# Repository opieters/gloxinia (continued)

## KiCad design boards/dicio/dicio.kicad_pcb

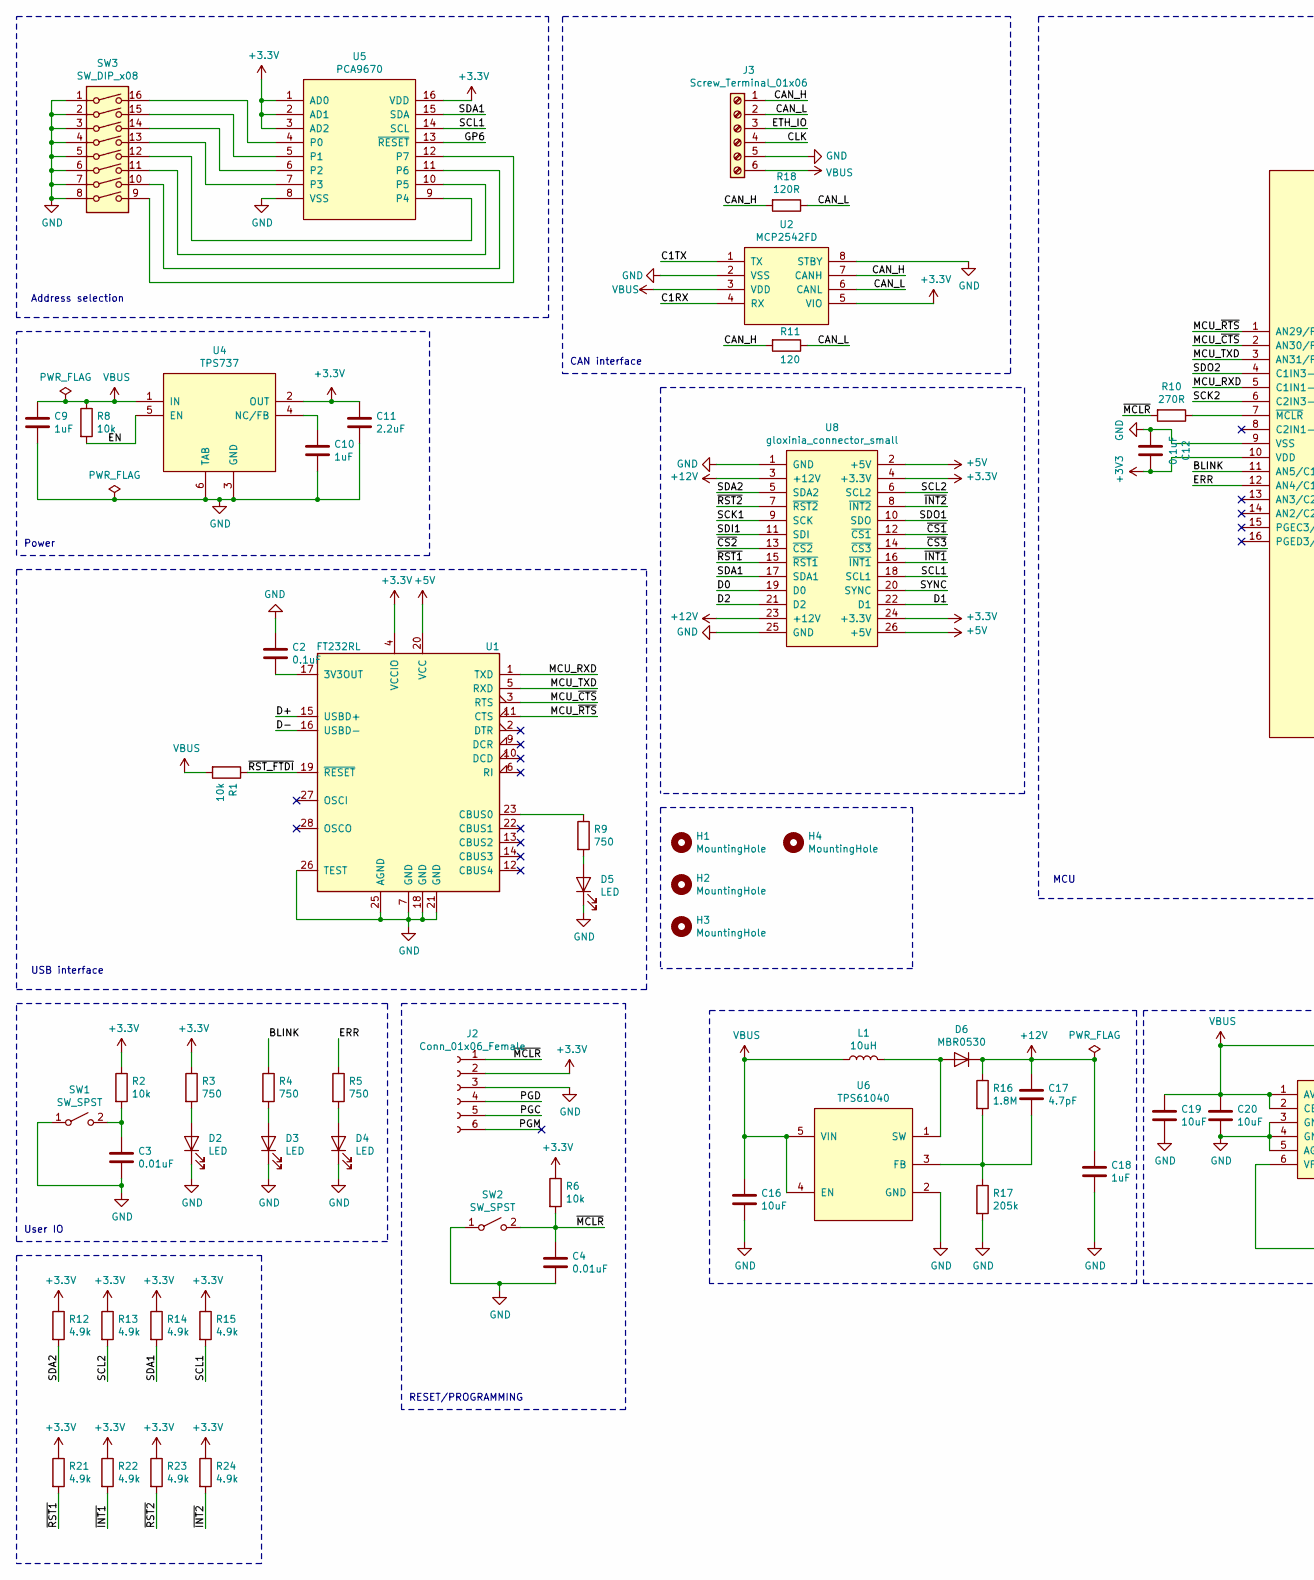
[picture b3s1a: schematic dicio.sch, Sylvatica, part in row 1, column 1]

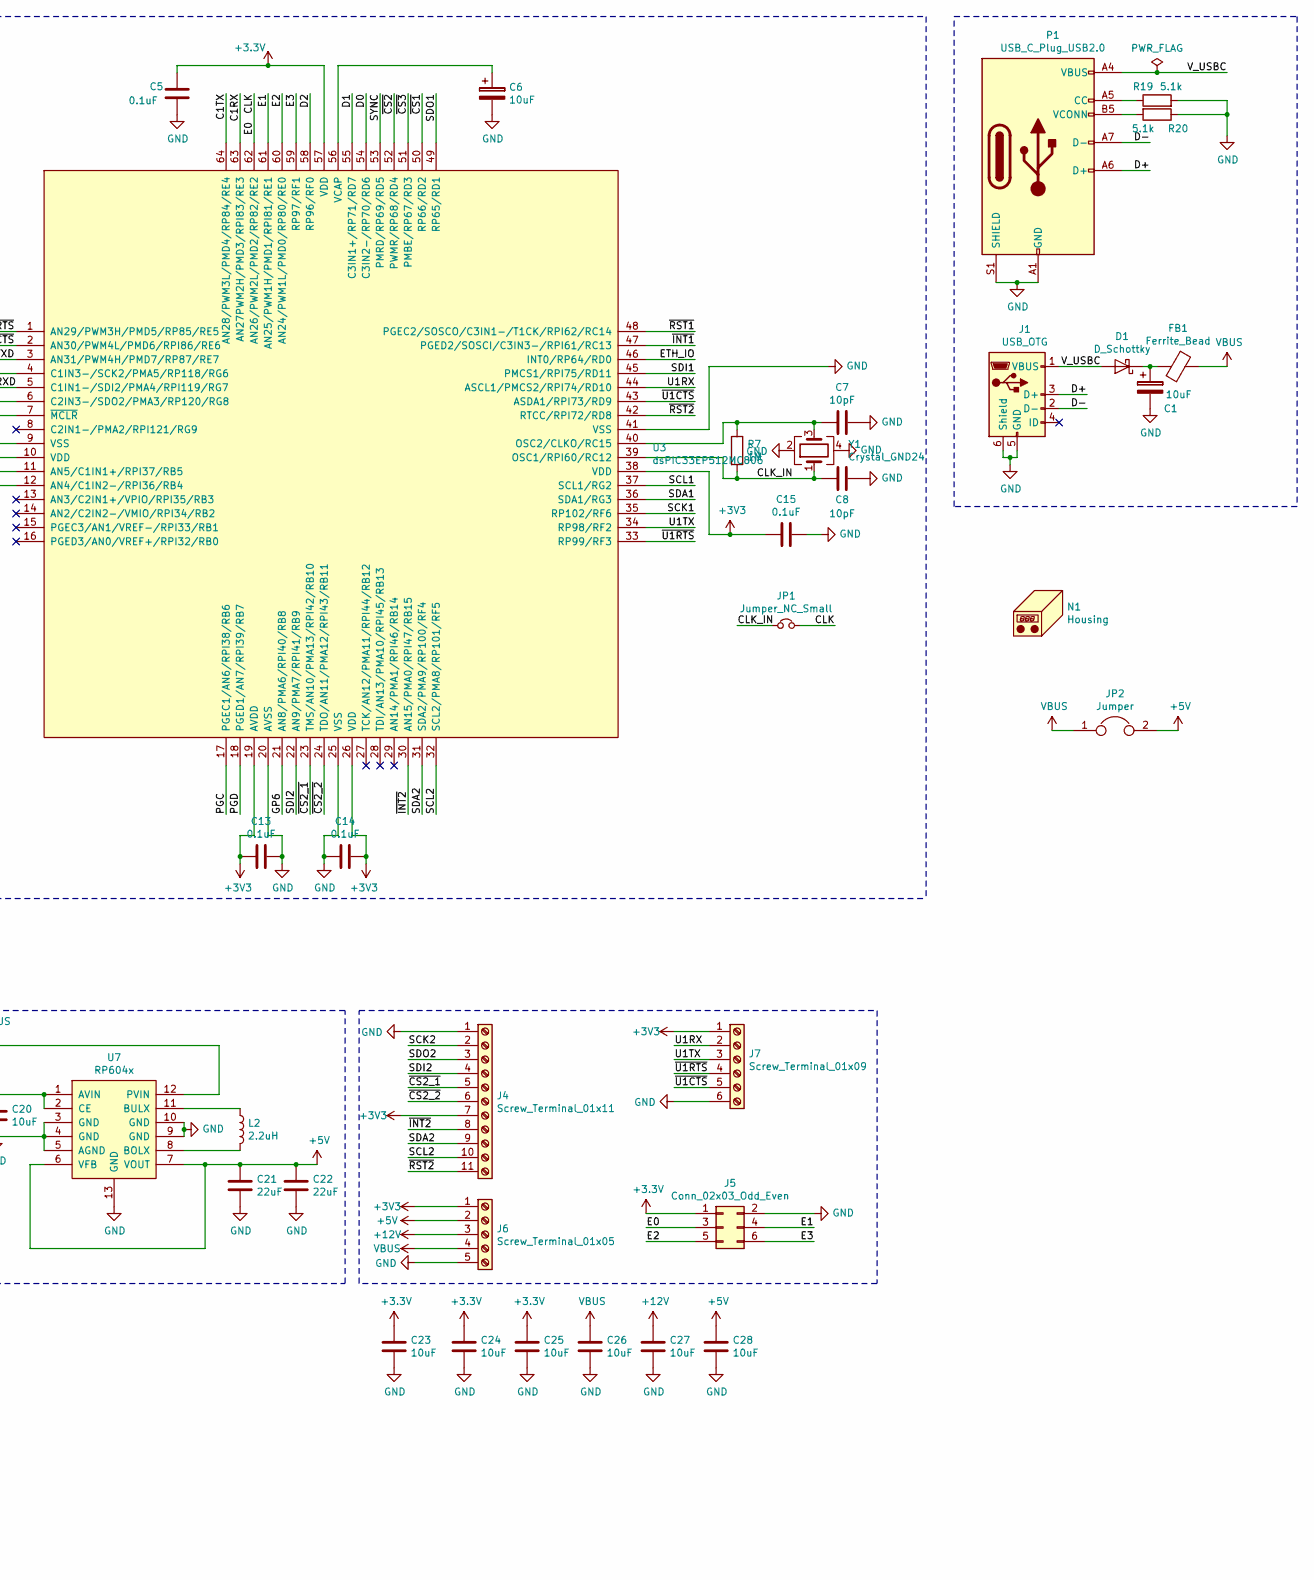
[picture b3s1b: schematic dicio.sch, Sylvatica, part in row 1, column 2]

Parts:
C1, C6, C16, C19, C20, C23, C24, C25, C26, C27, C28: 10uF; C_1210_3225Metric; Mouser 963-TMK325BJ106KM-P
C2, C5, C12, C13, C14, C15: 0.1uF; C_0603_1608Metric; Mouser 710-885012206071
C3, C4: 0.01uF; C_0603_1608Metric; Mouser 710-885012206065
C7, C8: 10pF; C_0603_1608Metric; Mouser 603-CC603FRNPO9BN100
C9, C10, C18: 1uF; C_0603_1608Metric; Mouser 963-TMK325B7105KD-T
C11: 2.2uF; C_1206_3216Metric; Mouser 791-1206X225K250CT
C17: 4.7pF; C_0603_1608Metric; Mouser 710-885012006049
C21, C22: 22uF; C_1210_3225Metric; Mouser 963-TMK316BBJ226ML-T
D1: D_Schottky; D_SMB; Mouser 621-B340LB-F
D2, D3, D4, D5: LED; LED_0603_1608Metric; Mouser 78-TLMS1000
D6: MBR0530; D_SOD-123; Mouser 512-MBR0530
FB1: Ferrite_Bead; L_0805_2012Metric; Mouser 875-MI0805K400R-10
H1, H2, H3, H4: MountingHole; MountingHole_3.2mm_M3
J1: USB_OTG; USB_Micro-B_Molex-105017-0001; Mouser 538-105017-0001
J2: Conn_01x06_Female; PinSocket_1x06_P2.54mm_Vertical
J3: Screw_Terminal_01x06; TB003-500-06; Mouser 490-TB003-500-P06BE
J4: Screw_Terminal_01x11; TB003-500-11; Mouser 490-TB003-500-P11BE
J5: Conn_02x03_Odd_Even; PinHeader_2x03_P2.54mm_Vertical
J6: Screw_Terminal_01x05; TB003-500-05; Mouser 490-TB003-500-P05BE
J7: Screw_Terminal_01x09; TB003-500-06; Mouser 490-TB003-500-P06BE
JP1: Jumper_NC_Small; SolderJumper-2_P1.3mm_Open_RoundedPad1.0x1.5mm
JP2: Jumper; SolderJumper-2_P1.3mm_Open_RoundedPad1.0x1.5mm
L1: 10uH; L_6.5mmx4.5mm_Bourns; Mouser 652-SDR0703-100KL
L2: 2.2uH; L_L4mm_D4mm_H1.8mm; Mouser 875-TYS40182R2M-10
N1: Housing; Enclosure-Hammond-1554LA; Mouser 546-1554LA2GYCL
P1: USB_C_Plug_USB2.0; USB_C_Receptacle_Amphenol_12401832E402A; Mouser 523-12401832E402A
R1, R2, R6, R8: 10k; R_0603_1608Metric; Mouser 284-APC0603B10K0N
R3, R4, R5, R9: 750; R_0603_1608Metric; Mouser 603-RC0603FR-07750RL
R7: 1M; R_0603_1608Metric; Mouser 603-RC0603FR-101ML
R10: 270R; R_0603_1608Metric; Mouser 603-RC0603FR-07270RL
R11: 120; R_0603_1608Metric; Mouser 71-CRCW0603120RFKEAC
R12, R13, R14, R15, R21, R22, R23, R24: 4.9k; R_0603_1608Metric; Mouser 603-RC0603FR-0724K9L
R16: 1.8M; C_0603_1608Metric; Mouser 603-AC0603FR-071M8L
R17: 205k; C_0603_1608Metric; Mouser 603-RC0603FR-07205KL
R18: 120R; R_Axial_DIN0204_L3.6mm_D1.6mm_P7.62mm_Horizontal; Mouser 594-5063JD120R0F
R19, R20: 5.1k; R_0603_1608Metric; Mouser 603-AC0603FR-135K1L
SW1, SW2: SW_SPST; SW_SPST_KMR2; Mouser 611-KMR621NGLFS
SW3: SW_DIP_x08; SW_DIP_SPSTx08_Slide_Omron_A6H-8101_W6.15mm_P1.27mm; Mouser 653-A6H-8101
U1: FT232RL; SSOP-28_5.3x10.2mm_P0.65mm; Mouser 895-FT232RL
U2: MCP2542FD; SOIC-8_3.9x4.9mm_P1.27mm; Mouser 579-MCP2542FDT-E/SN
U3: dsPIC33EP512MC806; TQFP-64_10x10mm_P0.5mm; Mouser 579-33EP512MC806IPT
U4: TPS737; SOT-223-6; Mouser 595-TPS73733DCQR
U5: PCA9670; TSSOP-16_4.4x5mm_P0.65mm; Mouser 771-PCA9670PW118
U6: TPS61040; SOT-23-5; Mouser 595-TPS61040DBVR
U7: RP604x; DFN_12_Pin_2.7x3mm_P0.5mm; Mouser 848-RP604K501A-TR
U8: gloxinia_connector_small; PinHeader_2x13_P2.54mm_Vertical; Mouser 200-SSQ11303TD
Y1: Crystal_GND24; Crystal_SMD_Abracon_ABM3B-4Pin_5.0x3.2mm; Mouser 520-80-10-30B-CWNT

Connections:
+5V: C21.1, C22.1, C28.1, J6.2, JP2.2, U1.20 (VCC), U7.6 (VFB), U7.7 (VOUT), U8.2 (+5V), U8.26 (+5V)
+12V: C17.1, C18.1, C27.1, D6.1 (K), J6.3, R16.1, U8.3 (+12V), U8.23 (+12V)
/BLINK: R4.1, U3.11 (AN5/C1IN1+/RPI37/RB5)
/C1RX: U2.4 (RX), U3.63 (AN27PWM2H/PMD3/RPI83/RE3)
/C1TX: U2.1 (TX), U3.64 (AN28/PWM3L/PMD4/RP84/RE4)
/CAN_H: J3.1, R11.2, R18.2, U2.7 (CANH)
/CAN_L: J3.2, R11.1, R18.1, U2.6 (CANL)
/CLK: J3.4, J5.3, JP1.2, U3.62 (AN26/PWM2L/PMD2/RP82/RE2)
/CLK_IN: C8.2, JP1.1, R7.2, U3.39 (OSC1/RPI60/RC12), Y1.1
/D0: U3.54 (C3IN2-/RP70/RD6), U8.19 (D0)
/D1: U3.55 (C3IN1+/RP71/RD7), U8.22 (D1)
/D2: U3.58 (RP96/RF0), U8.21 (D2)
/D+: J1.3 (D+), P1.A6 (D+), U1.15 (USBD+)
/D-: J1.2 (D-), P1.A7 (D-), U1.16 (USBD-)
/E1: J5.4, U3.61 (AN25/PWM1H/PMD1/RPI81/RE1)
/E2: J5.5, U3.60 (AN24/PWM1L/PMD0/RP80/RE0)
/E3: J5.6, U3.59 (RP97/RF1)
/EN: R8.2, U4.5 (EN)
/ERR: R5.1, U3.12 (AN4/C1IN2-/RPI36/RB4)
/ETH_IO: J3.3, U3.46 (INT0/RP64/RD0)
/GP6: U3.21 (AN8/PMA6/RPI40/RB8), U5.13 (~RESET)
/MCU_RXD: U1.1 (TXD), U3.5 (C1IN1-/SDI2/PMA4/RPI119/RG7)
/MCU_TXD: U1.5 (RXD), U3.3 (AN31/PWM4H/PMD7/RP87/RE7)
/MCU_~CTS: U1.3 (RTS), U3.2 (AN30/PWM4L/PMD6/RPI86/RE6)
/MCU_~RTS: U1.11 (CTS), U3.1 (AN29/PWM3H/PMD5/RP85/RE5)
/PGC: J2.5, U3.17 (PGEC1/AN6/RPI38/RB6)
/PGD: J2.4, U3.18 (PGED1/AN7/RPI39/RB7)
/PGM: J2.6
/SCK1: U3.35 (RP102/RF6), U8.9 (SCK)
/SCK2: J4.2, U3.6 (C2IN3-/SDO2/PMA3/RP120/RG8)
/SCL1: R15.2, U3.37 (SCL1/RG2), U5.14 (SCL), U8.18 (SCL1)
/SCL2: J4.10, R13.2, U3.32 (SCL2/PMA8/RP101/RF5), U8.6 (SCL2)
/SDA1: R14.2, U3.36 (SDA1/RG3), U5.15 (SDA), U8.17 (SDA1)
/SDA2: J4.9, R12.2, U3.31 (SDA2/PMA9/RP100/RF4), U8.5 (SDA2)
/SDI1: U3.45 (PMCS1/RPI75/RD11), U8.11 (SDI)
/SDI2: J4.4, U3.22 (AN9/PMA7/RPI41/RB9)
/SDO1: U3.49 (RP65/RD1), U8.10 (SDO)
/SDO2: J4.3, U3.4 (C1IN3-/SCK2/PMA5/RP118/RG6)
/SYNC: U3.53 (PMRD/RP69/RD5), U8.20 (SYNC)
/U1RX: J7.2, U3.44 (ASCL1/PMCS2/RPI74/RD10)
/U1TX: J7.3, U3.34 (RP98/RF2)
/V_USBC: D1.2 (A), J1.1 (VBUS), P1.A4 (VBUS), P1.A9 (VBUS), P1.B4 (VBUS), P1.B9 (VBUS)
/~CS1: U3.50 (RP66/RD2), U8.12 (~CS1)
/~CS2: U3.52 (PWMR/RP68/RD4), U8.13 (~CS2)
/~CS2_1: J4.5, U3.23 (TMS/AN10/PMA13/RPI42/RB10)
/~CS2_2: J4.6, U3.24 (TDO/AN11/PMA12/RPI43/RB11)
/~CS3: U3.51 (PMBE/RP67/RD3), U8.14 (~CS3)
/~INT1: R22.2, U3.47 (PGED2/SOSCI/C3IN3-/RPI61/RC13), U8.16 (~INT1)
/~INT2: J4.8, R24.2, U3.30 (AN15/PMA0/RPI47/RB15), U8.8 (~INT2)
/~MCLR: C4.1, J2.1, R6.2, R10.2, SW2.2 (B)
/~RST1: R21.2, U3.48 (PGEC2/SOSCO/C3IN1-/T1CK/RPI62/RC14), U8.15 (~RST1)
/~RST2: J4.11, R23.2, U3.42 (RTCC/RPI72/RD8), U8.7 (~RST2)
/~RST_FTDI: R1.1, U1.19 (~RESET~)
/~U1CTS: J7.5, U3.43 (ASDA1/RPI73/RD9)
/~U1RTS: J7.4, U3.33 (RP99/RF3)
GND: C1.2, C2.1, C3.2, C4.2, C5.2, C6.2, C7.1, C8.1, C9.2, C10.2, C11.2, C12.2, C13.1, C14.2, C15.2, C16.2, C18.2, C19.2, C20.2, C21.2, C22.2, C23.2, C24.2, C25.2, C26.2, C27.2, C28.2, D2.1 (K), D3.1 (K), D4.1 (K), D5.1 (K), J1.5 (GND), J1.6 (Shield), J2.3, J3.5, J4.1, J5.2, J6.5, J7.6, P1.A1 (GND), P1.A12 (GND), P1.B1 (GND), P1.B12 (GND), P1.S1 (SHIELD), R17.2, R19.2, R20.1, SW1.1 (A), SW2.1 (A), SW3.1, SW3.2, SW3.3, SW3.4, SW3.5, SW3.6, SW3.7, SW3.8, U1.7 (GND), U1.18 (GND), U1.21 (GND), U1.25 (AGND), U1.26 (TEST), U2.2 (VSS), U2.8 (STBY), U3.9 (VSS), U3.20 (AVSS), U3.25 (VSS), U3.41 (VSS), U4.3 (GND), U4.6 (TAB), U5.8 (VSS), U6.2 (GND), U7.3 (GND), U7.4 (GND), U7.5 (AGND), U7.9 (GND), U7.10 (GND), U7.13 (GND), U8.1 (GND), U8.25 (GND), Y1.2, Y1.4
unnamed: C1.1, D1.1 (K), FB1.2
unnamed: C2.2, U1.17 (3V3OUT)
unnamed: C3.1, R2.2, SW1.2 (B)
unnamed: C6.1, U3.56 (VCAP)
unnamed: C7.2, R7.1, U3.40 (OSC2/CLKO/RC15), Y1.3
unnamed: C10.1, U4.4 (NC/FB)
unnamed: C17.2, R16.2, R17.1, U6.3 (FB)
unnamed: D2.2 (A), R3.2
unnamed: D3.2 (A), R4.2
unnamed: D4.2 (A), R5.2
unnamed: D5.2 (A), R9.2
unnamed: D6.2 (A), L1.2, U6.1 (SW)
unnamed: L2.1, U7.11 (BULX)
unnamed: L2.2, U7.8 (BOLX)
unnamed: P1.A5 (CC), R19.1
unnamed: P1.B5 (VCONN), R20.2
unnamed: R9.1, U1.23 (CBUS0)
unnamed: R10.1, U3.7 (~MCLR)
unnamed: SW3.9, U5.12 (P7)
unnamed: SW3.10, U5.11 (P6)
unnamed: SW3.11, U5.10 (P5)
unnamed: SW3.12, U5.9 (P4)
unnamed: SW3.13, U5.7 (P3)
unnamed: SW3.14, U5.6 (P2)
unnamed: SW3.15, U5.5 (P1)
unnamed: SW3.16, U5.4 (P0)
VBUS: C9.1, C16.1, C19.1, C20.1, C26.1, FB1.1, J3.6, J6.4, JP2.1, L1.1, R1.2, R8.1, U2.3 (VDD), U4.1 (IN), U6.4 (EN), U6.5 (VIN), U7.1 (AVIN), U7.2 (CE), U7.12 (PVIN)

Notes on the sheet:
CAN interface
RESET/PROGRAMMING
User IO
USB interface
Power
MCU
Address selection

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
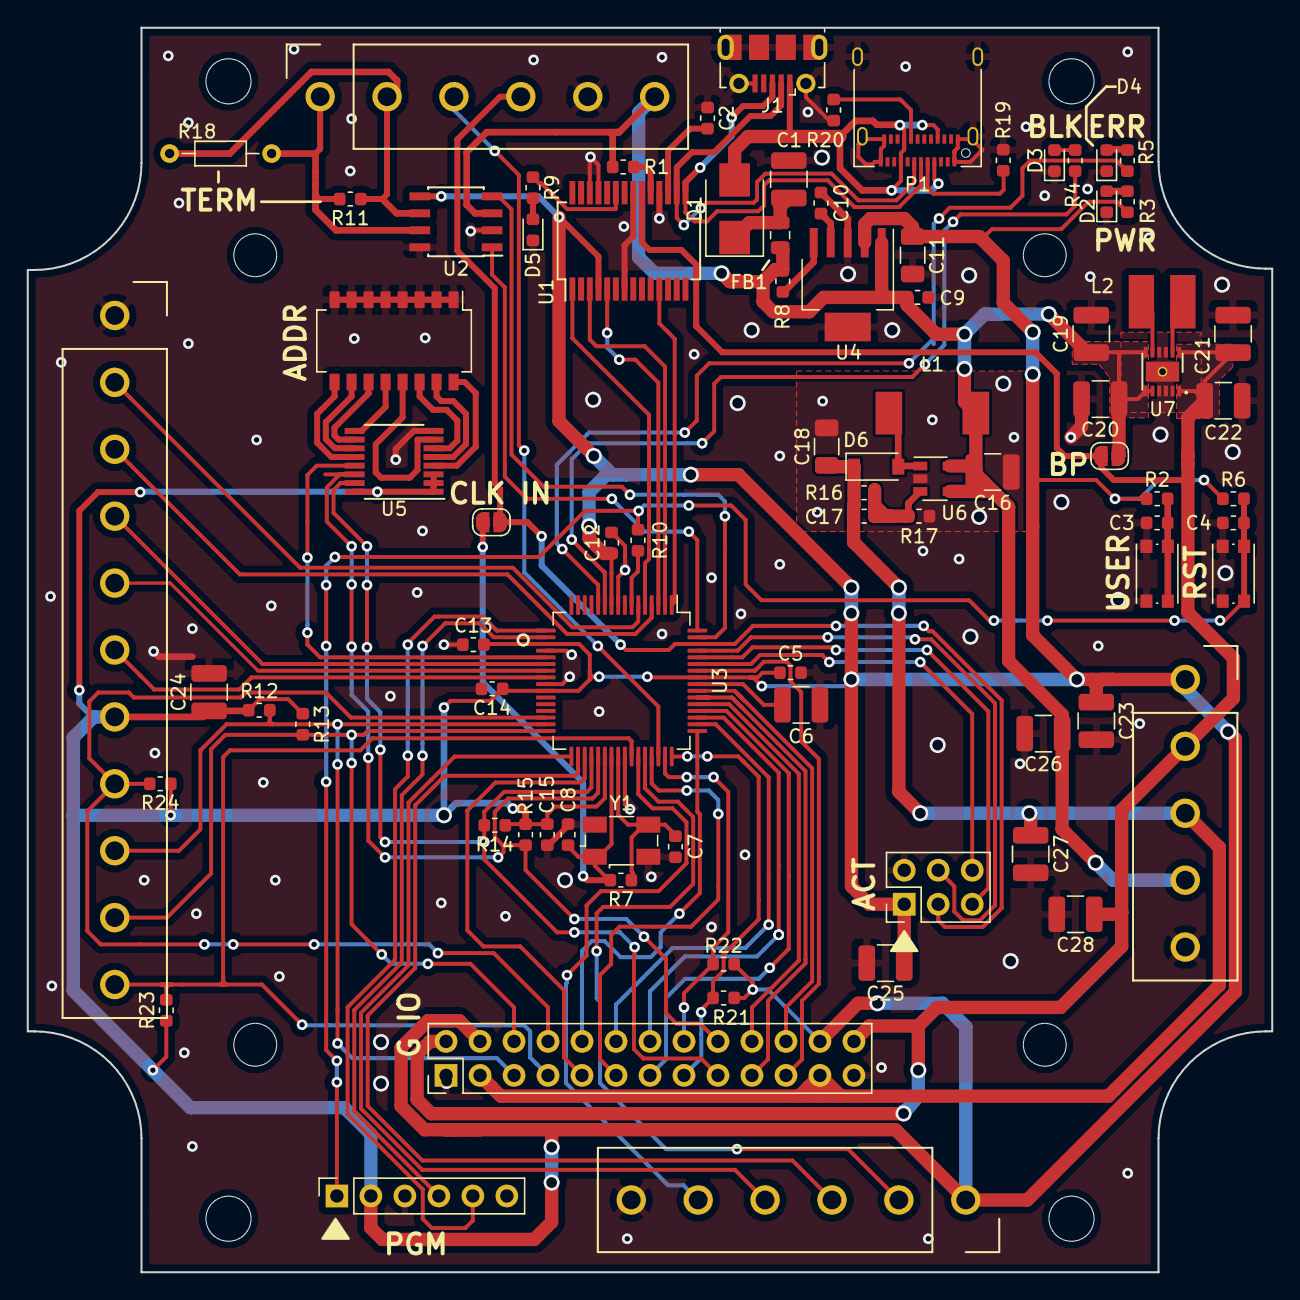
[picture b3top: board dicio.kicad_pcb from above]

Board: 2 copper layers, 93.0 x 93.0 mm, 88 parts (0 on the bottom side), 83 nets.

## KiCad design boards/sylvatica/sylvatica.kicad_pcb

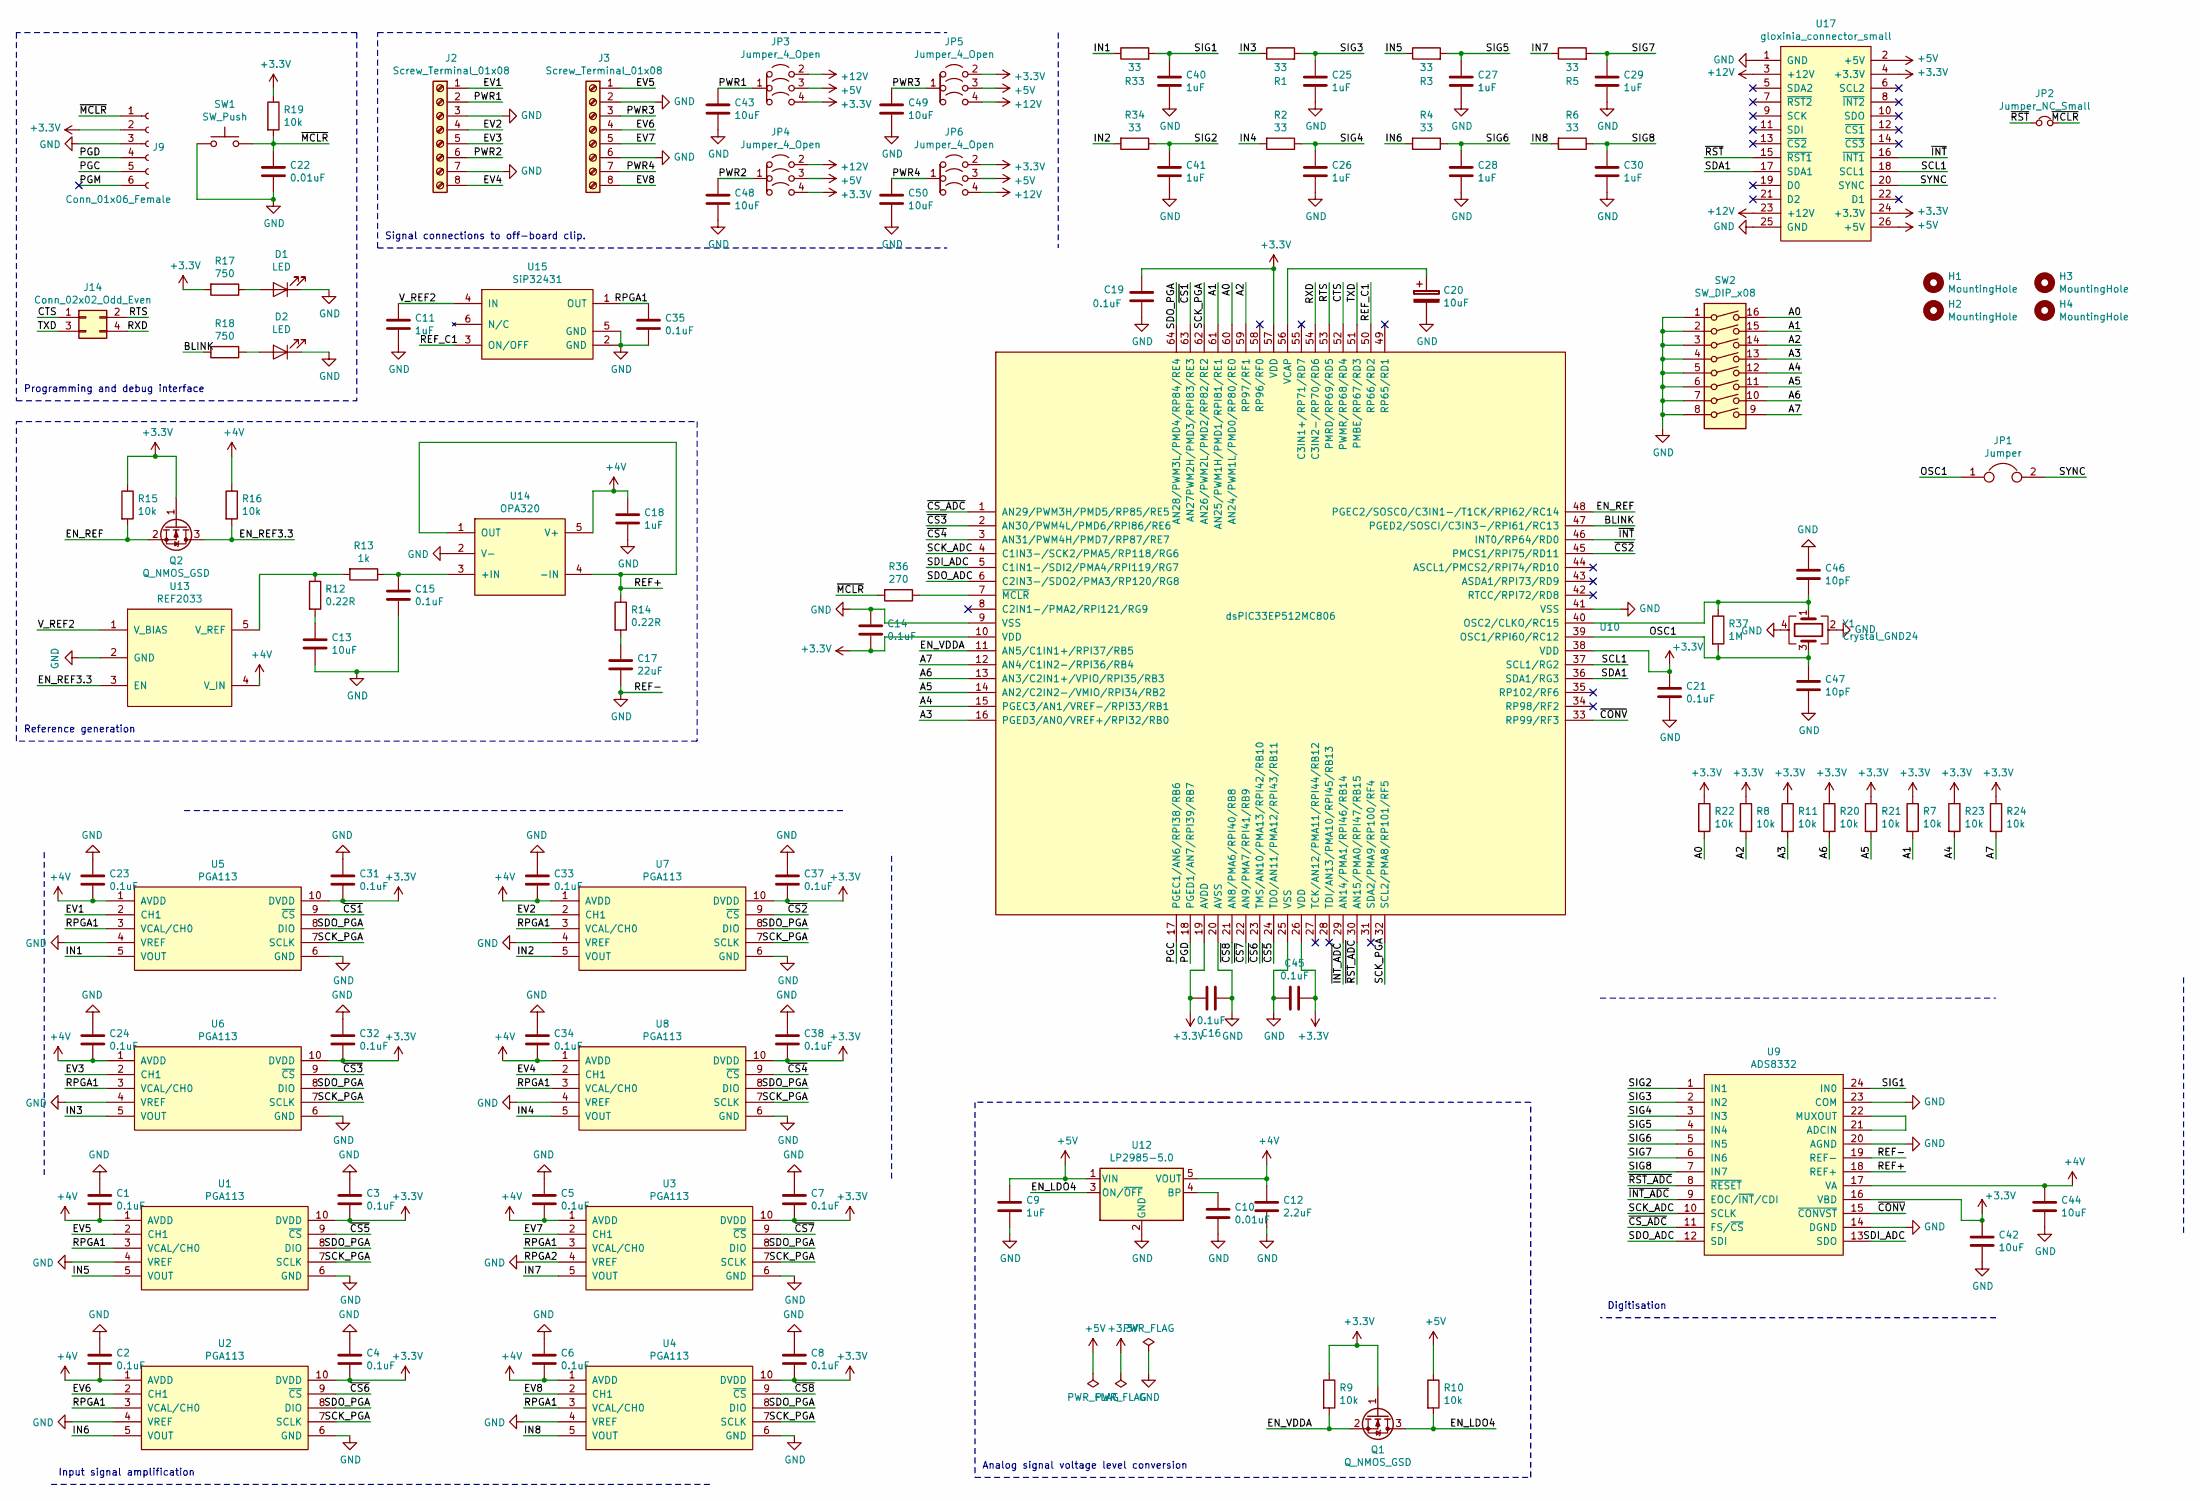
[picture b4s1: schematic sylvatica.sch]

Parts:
C1, C2, C3, C4, C5, C6, C7, C8, C14, C15, C16, C19, C21, C23, C24, C31, C32, C33, C34, C35, C37, C38, C45: 0.1uF; C_0603_1608Metric; Mouser 710-885012206071
C9, C11, C25, C26, C27, C28, C29, C30, C40, C41: 1uF; C_0603_1608Metric; Mouser 77-VJ0603A102GXJPBC
C10, C22: 0.01uF; C_0603_1608Metric; Mouser 77-VJ0603A102GXJPBC
C12: 2.2uF; C_1206_3216Metric; Mouser 791-1206X225K250CT
C13, C20, C42, C43, C44, C48, C49, C50: 10uF; C_1210_3225Metric; Mouser 963-TMK325BJ106KM-P
C17: 22uF; C_1206_3216Metric; Mouser 963-TMK316BBJ226ML-T
C18: 1uF; C_1210_3225Metric; Mouser 963-TMK325B7105KD-T
C46, C47: 10pF; C_0603_1608Metric; Mouser 603-CC603FRNPO9BN100
D1, D2: LED; LED_0603_1608Metric; Mouser 78-TLMS1000
H1, H2, H3, H4: MountingHole; MountingHole_3.2mm_M3
J2, J3: Screw_Terminal_01x08; TB001-500-08; Mouser 490-TB003-500-P08BE
J9: Conn_01x06_Female; PinSocket_1x06_P2.54mm_Vertical
J14: Conn_02x02_Odd_Even; PinSocket_2x02_P2.54mm_Vertical
JP1: Jumper; SolderJumper-2_P1.3mm_Open_Pad1.0x1.5mm
JP2: Jumper_NC_Small; SolderJumper-2_P1.3mm_Open_RoundedPad1.0x1.5mm
JP3, JP4, JP5, JP6: Jumper_4_Open; SolderJumper-4_Open_Pad1.0x1.5mm
Q1, Q2: Q_NMOS_GSD; SOT-23; Mouser 512-BSS138
R1, R2, R3, R4, R5, R6, R33, R34: 33; R_0603_1608Metric; Mouser 603-RC0603FR-0733RL
R7, R8, R9, R10, R11, R15, R16, R19, R20, R21, R22, R23, R24: 10k; R_0603_1608Metric; Mouser 284-APC0603B10K0N
R12, R14: 0.22R; R_0603_1608Metric; Mouser 667-ERJ-3RQFR22V
R13: 1k; R_0603_1608Metric; Mouser 652-CR0603-FX1001HLF
R17, R18: 750; R_0603_1608Metric; Mouser 603-RC0603FR-07750RL
R36: 270; R_0603_1608Metric; Mouser 603-RC0603FR-07270RL
R37: 1M; R_0603_1608Metric; Mouser 603-RC0603FR-101ML
SW1: SW_Push; SW_SPST_KMR2; Mouser 611-KMR621NGLFS
SW2: SW_DIP_x08; SW_DIP_SPSTx08_Slide_Omron_A6H-8101_W6.15mm_P1.27mm; Mouser 653-A6H-8101
U1, U2, U3, U4, U5, U6, U7, U8: PGA113; MSOP-10_3x3mm_P0.5mm; Mouser 595-PGA113AIDGSR
U9: ADS8332; TSSOP-24_4.4x7.8mm_P0.65mm; Mouser 595-ADS8332IBPWR
U10: dsPIC33EP512MC806; TQFP-64_10x10mm_P0.5mm; Mouser 579-33EP512MC806IPT
U12: LP2985-5.0; SOT-23-5; Mouser 926-LP2985IM540NOPB
U13: REF2033; SOT-23-5; Mouser 595-REF2033AIDDCR
U14: OPA320; SOT-23-5; Mouser 595-OPA320AIDBVR
U15: SiP32431; SOT-363_SC-70-6; Mouser 781-SIP32431DR3-GE3
U17: gloxinia_connector_small; PinHeader_2x13_P2.54mm_Vertical; Mouser 200-SSQ11303TD
Y1: Crystal_GND24; Crystal_SMD_Abracon_ABM3B-4Pin_5.0x3.2mm; Mouser 520-80-10-30B-CWNT

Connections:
+3V3: C3.2, C4.2, C7.2, C8.2, C14.2, C16.1, C19.1, C21.1, C31.2, C32.2, C37.2, C38.2, C42.1, C45.1, J9.2, JP3.4 (B), JP4.4 (B), JP5.2 (B), JP6.2 (B), Q1.1 (G), Q2.1 (G), R7.1, R8.1, R9.1, R11.1, R15.1, R17.2, R19.1, R20.1, R21.1, R22.1, R23.1, R24.1, U1.10 (DVDD), U2.10 (DVDD), U3.10 (DVDD), U4.10 (DVDD), U5.10 (DVDD), U6.10 (DVDD), U7.10 (DVDD), U8.10 (DVDD), U9.16 (VBD), U10.10 (VDD), U10.19 (AVDD), U10.26 (VDD), U10.38 (VDD), U10.57 (VDD), U17.4 (+3.3V), U17.24 (+3.3V)
+4V: C1.2, C2.2, C5.2, C6.2, C12.1, C18.1, C23.2, C24.2, C33.2, C34.2, C44.1, R16.1, U1.1 (AVDD), U2.1 (AVDD), U3.1 (AVDD), U4.1 (AVDD), U5.1 (AVDD), U6.1 (AVDD), U7.1 (AVDD), U8.1 (AVDD), U9.17 (VA), U12.5 (VOUT), U13.4 (V_IN), U14.5 (V+)
+5V: C9.1, JP3.3 (B), JP4.3 (B), JP5.3 (B), JP6.3 (B), R10.1, U12.1 (VIN), U17.2 (+5V), U17.26 (+5V)
+12V: JP3.2 (B), JP4.2 (B), JP5.4 (B), JP6.4 (B), U17.3 (+12V), U17.23 (+12V)
/A0: R22.2, SW2.16, U10.60 (AN24/PWM1L/PMD0/RP80/RE0)
/A1: R7.2, SW2.15, U10.61 (AN25/PWM1H/PMD1/RPI81/RE1)
/A2: R8.2, SW2.14, U10.59 (RP97/RF1)
/A3: R11.2, SW2.13, U10.16 (PGED3/AN0/VREF+/RPI32/RB0)
/A4: R23.2, SW2.12, U10.15 (PGEC3/AN1/VREF-/RPI33/RB1)
/A5: R21.2, SW2.11, U10.14 (AN2/C2IN2-/VMIO/RPI34/RB2)
/A6: R20.2, SW2.10, U10.13 (AN3/C2IN1+/VPIO/RPI35/RB3)
/A7: R24.2, SW2.9, U10.12 (AN4/C1IN2-/RPI36/RB4)
/BLINK: R18.2, U10.47 (PGED2/SOSCI/C3IN3-/RPI61/RC13)
/CTS: J14.1, U10.52 (PWMR/RP68/RD4)
/EN_LDO4: Q1.3 (D), R10.2, U12.3 (ON/~OFF~)
/EN_REF: Q2.2 (S), R15.2, U10.48 (PGEC2/SOSCO/C3IN1-/T1CK/RPI62/RC14)
/EN_REF3.3: Q2.3 (D), R16.2, U13.3 (EN)
/EN_VDDA: Q1.2 (S), R9.2, U10.11 (AN5/C1IN1+/RPI37/RB5)
/EV1: J2.1, U5.2 (CH1)
/EV2: J2.4, U7.2 (CH1)
/EV3: J2.5, U6.2 (CH1)
/EV4: J2.8, U8.2 (CH1)
/EV5: J3.1, U1.2 (CH1)
/EV6: J3.4, U2.2 (CH1)
/EV7: J3.5, U3.2 (CH1)
/EV8: J3.8, U4.2 (CH1)
/IN1: R33.1, U5.5 (VOUT)
/IN2: R34.2, U7.5 (VOUT)
/IN3: R1.1, U6.5 (VOUT)
/IN4: R2.2, U8.5 (VOUT)
/IN5: R3.1, U1.5 (VOUT)
/IN6: R4.2, U2.5 (VOUT)
/IN7: R5.1, U3.5 (VOUT)
/IN8: R6.2, U4.5 (VOUT)
/OSC1: C47.1, JP1.1, R37.2, U10.39 (OSC1/RPI60/RC12), Y1.3
/PGC: J9.5, U10.17 (PGEC1/AN6/RPI38/RB6)
/PGD: J9.4, U10.18 (PGED1/AN7/RPI39/RB7)
/PGM: J9.6
/PWR1: C43.1, J2.2, JP3.1 (A)
/PWR2: C48.1, J2.6, JP4.1 (A)
/PWR3: C49.1, J3.3, JP5.1 (A)
/PWR4: C50.1, J3.7, JP6.1 (A)
/REF+: R14.1, U9.18 (REF+), U14.1 (OUT), U14.4 (-IN)
/REF_C1: U10.50 (RP66/RD2), U15.3 (ON/OFF)
/RPGA1: C35.1, U1.3 (VCAL/CH0), U2.3 (VCAL/CH0), U3.3 (VCAL/CH0), U4.3 (VCAL/CH0), U5.3 (VCAL/CH0), U6.3 (VCAL/CH0), U7.3 (VCAL/CH0), U8.3 (VCAL/CH0), U15.1 (OUT)
/RTS: J14.2, U10.53 (PMRD/RP69/RD5)
/RXD: J14.4, U10.54 (C3IN2-/RP70/RD6)
/SCK_ADC: U9.10 (SCLK), U10.4 (C1IN3-/SCK2/PMA5/RP118/RG6)
/SCK_PGA: U1.7 (SCLK), U2.7 (SCLK), U3.7 (SCLK), U4.7 (SCLK), U5.7 (SCLK), U6.7 (SCLK), U7.7 (SCLK), U8.7 (SCLK), U10.32 (SCL2/PMA8/RP101/RF5), U10.62 (AN26/PWM2L/PMD2/RP82/RE2)
/SCL1: U10.37 (SCL1/RG2), U17.18 (SCL1)
/SDA1: U10.36 (SDA1/RG3), U17.17 (SDA1)
/SDI_ADC: U9.13 (SDO), U10.5 (C1IN1-/SDI2/PMA4/RPI119/RG7)
/SDO_ADC: U9.12 (SDI), U10.6 (C2IN3-/SDO2/PMA3/RP120/RG8)
/SDO_PGA: U1.8 (DIO), U2.8 (DIO), U3.8 (DIO), U4.8 (DIO), U5.8 (DIO), U6.8 (DIO), U7.8 (DIO), U8.8 (DIO), U10.64 (AN28/PWM3L/PMD4/RP84/RE4)
/SIG1: C40.1, R33.2, U9.24 (IN0)
/SIG2: C41.1, R34.1, U9.1 (IN1)
/SIG3: C25.1, R1.2, U9.2 (IN2)
/SIG4: C26.1, R2.1, U9.3 (IN3)
/SIG5: C27.1, R3.2, U9.4 (IN4)
/SIG6: C28.1, R4.1, U9.5 (IN5)
/SIG7: C29.1, R5.2, U9.6 (IN6)
/SIG8: C30.1, R6.1, U9.7 (IN7)
/SYNC: JP1.2, U17.20 (SYNC)
/TXD: J14.3, U10.51 (PMBE/RP67/RD3)
/V_REF2: C11.1, U13.1 (V_BIAS), U15.4 (IN)
/~CONV: U9.15 (~CONVST), U10.33 (RP99/RF3)
/~CS1: U5.9 (~CS), U10.63 (AN27PWM2H/PMD3/RPI83/RE3)
/~CS2: U7.9 (~CS), U10.45 (PMCS1/RPI75/RD11)
/~CS3: U6.9 (~CS), U10.2 (AN30/PWM4L/PMD6/RPI86/RE6)
/~CS4: U8.9 (~CS), U10.3 (AN31/PWM4H/PMD7/RP87/RE7)
/~CS5: U1.9 (~CS), U10.24 (TDO/AN11/PMA12/RPI43/RB11)
/~CS6: U2.9 (~CS), U10.23 (TMS/AN10/PMA13/RPI42/RB10)
/~CS7: U3.9 (~CS), U10.22 (AN9/PMA7/RPI41/RB9)
/~CS8: U4.9 (~CS), U10.21 (AN8/PMA6/RPI40/RB8)
/~CS_ADC: U9.11 (FS/~CS), U10.1 (AN29/PWM3H/PMD5/RP85/RE5)
/~INT: U10.46 (INT0/RP64/RD0), U17.16 (~INT1)
/~INT_ADC: U9.9 (EOC/~INT~/CDI), U10.29 (AN14/PMA1/RPI46/RB14)
/~MCLR: C22.1, J9.1, JP2.2, R19.2, R36.2, SW1.2
/~RST: JP2.1, U17.15 (~RST1)
/~RST_ADC: U9.8 (~RESET), U10.30 (AN15/PMA0/RPI47/RB15)
GND: C1.1, C2.1, C3.1, C4.1, C5.1, C6.1, C7.1, C8.1, C9.2, C10.2, C11.2, C12.2, C13.2, C14.1, C15.2, C16.2, C17.2, C18.2, C19.2, C20.2, C21.2, C22.2, C23.1, C24.1, C25.2, C26.2, C27.2, C28.2, C29.2, C30.2, C31.1, C32.1, C33.1, C34.1, C35.2, C37.1, C38.1, C40.2, C41.2, C42.2, C43.2, C44.2, C45.2, C46.1, C47.2, C48.2, C49.2, C50.2, D1.1 (K), D2.1 (K), J2.3, J2.7, J3.2, J3.6, J9.3, SW1.1, SW2.1, SW2.2, SW2.3, SW2.4, SW2.5, SW2.6, SW2.7, SW2.8, U1.4 (VREF), U1.6 (GND), U2.4 (VREF), U2.6 (GND), U3.4 (VREF), U3.6 (GND), U4.4 (VREF), U4.6 (GND), U5.4 (VREF), U5.6 (GND), U6.4 (VREF), U6.6 (GND), U7.4 (VREF), U7.6 (GND), U8.4 (VREF), U8.6 (GND), U9.14 (DGND), U9.19 (REF-), U9.20 (AGND), U9.23 (COM), U10.9 (VSS), U10.20 (AVSS), U10.25 (VSS), U10.41 (VSS), U12.2 (GND), U13.2 (GND), U14.2 (V-), U15.2 (GND), U15.5 (GND), U17.1 (GND), U17.25 (GND), Y1.2, Y1.4
unnamed: C10.1, U12.4 (BP)
unnamed: C13.1, R12.2
unnamed: C15.1, R13.1, U14.3 (+IN)
unnamed: C17.1, R14.2
unnamed: C20.1, U10.56 (VCAP)
unnamed: C46.2, R37.1, U10.40 (OSC2/CLKO/RC15), Y1.1
unnamed: D1.2 (A), R17.1
unnamed: D2.2 (A), R18.1
unnamed: R12.1, R13.2, U13.5 (V_REF)
unnamed: R36.1, U10.7 (~MCLR)
unnamed: U9.21 (ADCIN), U9.22 (MUXOUT)

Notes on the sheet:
Signal connections to off-board clip.
Programming and debug interface
Input signal amplification
Reference generation
Analog signal voltage level conversion
Digitisation

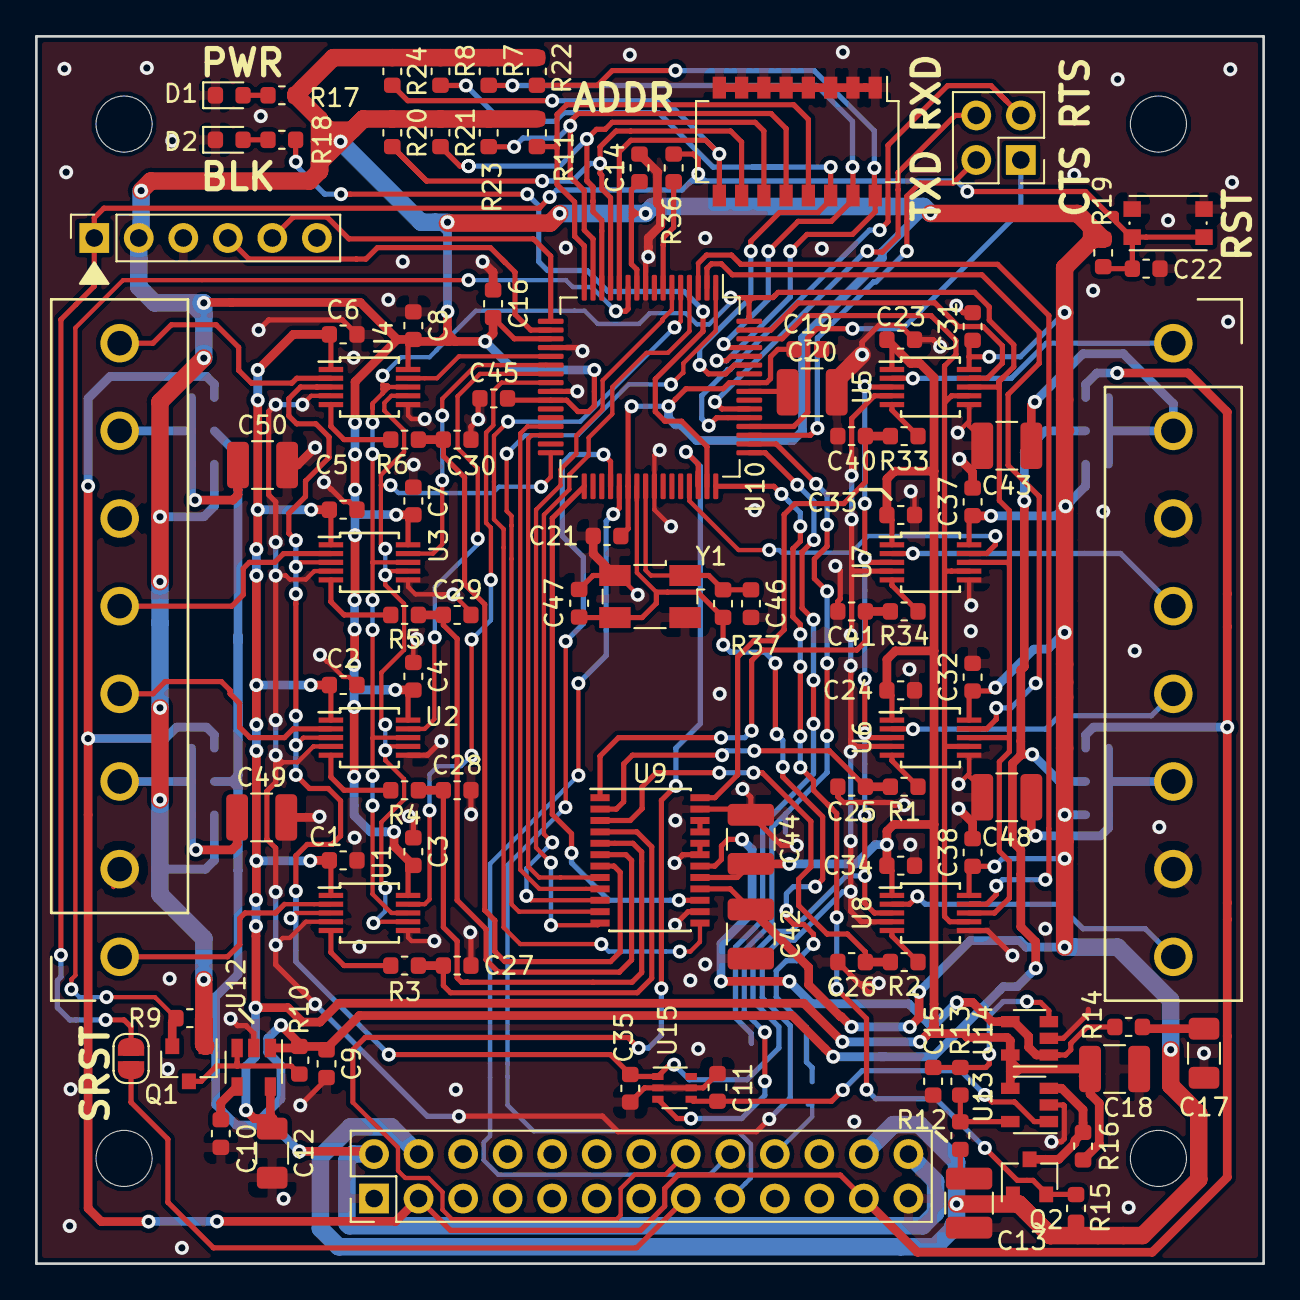
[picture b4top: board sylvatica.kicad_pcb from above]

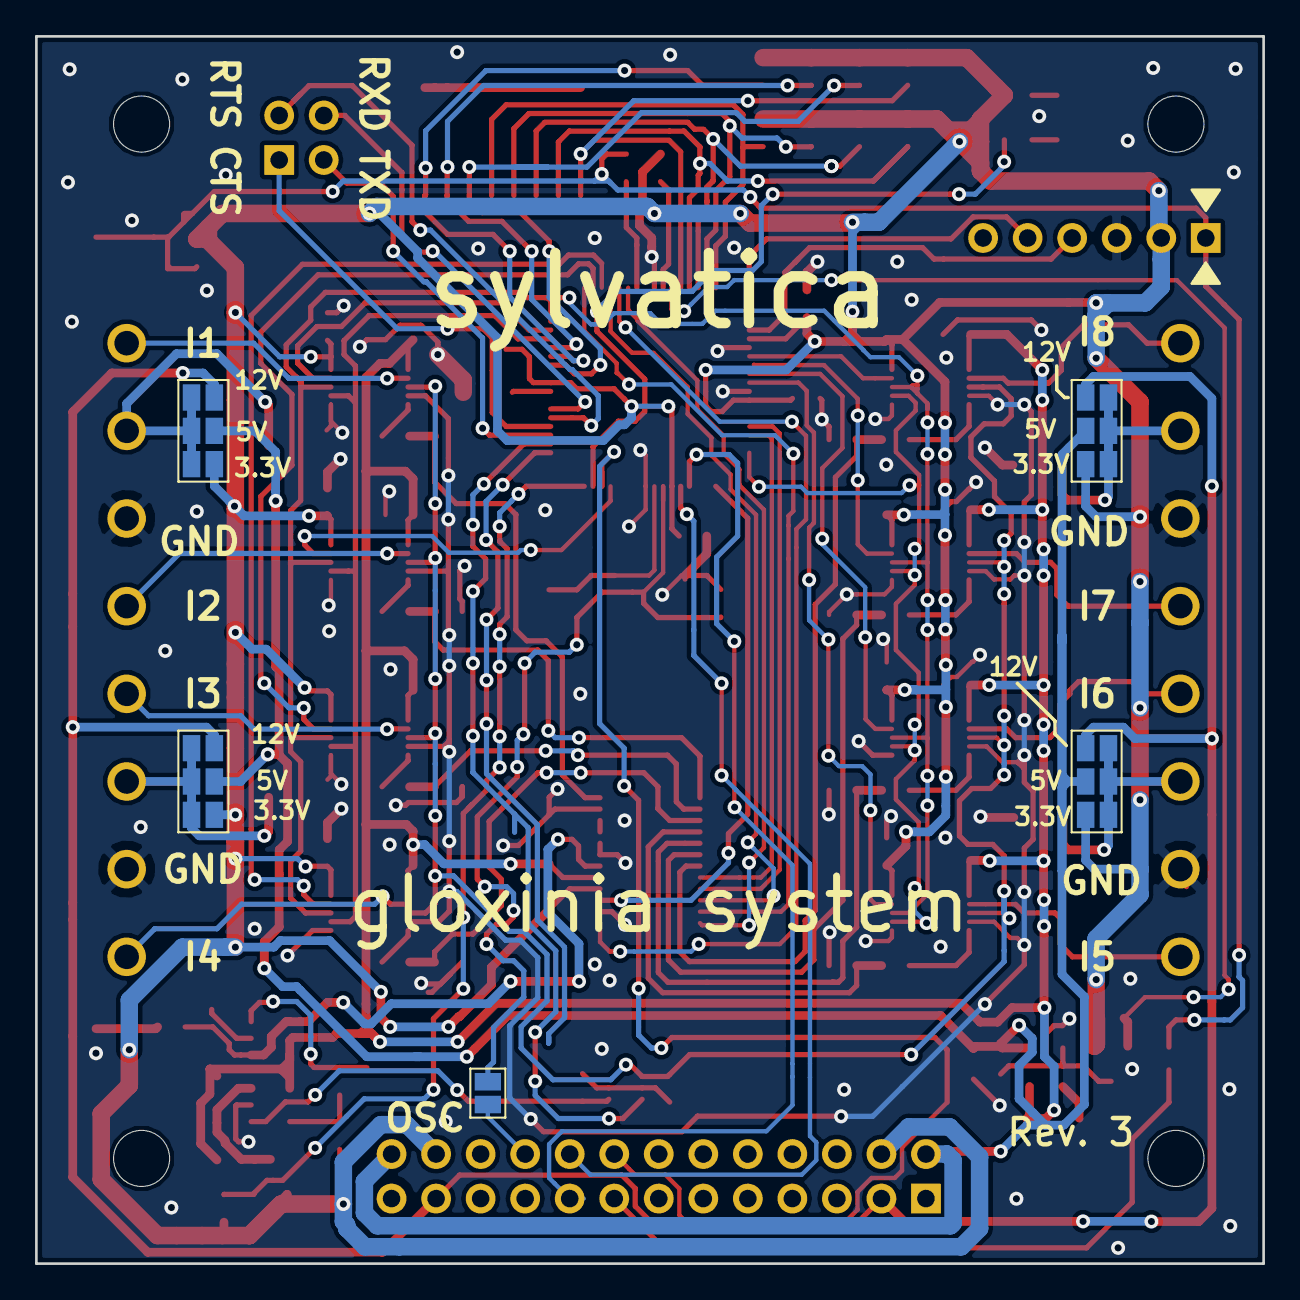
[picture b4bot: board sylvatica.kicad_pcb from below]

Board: 2 copper layers, 70.0 x 70.0 mm, 112 parts (5 on the bottom side), 91 nets.

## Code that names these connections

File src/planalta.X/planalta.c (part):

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    .spi_module = SPI_MODULE_SELECTOR_2,\
    .rst_pin = PIN_INIT(B, 3),\
    .cs_pin = PIN_INIT(E, 5),\
    .conv_pin = PIN_INIT(E, 7)} 

#define PLANALTA_PGA0 {      \
    .channel = PGA_MUX_CH1,   \
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    _TRISG3 = 0;
    _ODCD0 = 1; // nINT
    _TRISD0 = 0;
    _RD0 = 1;
    
    // UART
    _TRISD3 = 1; // U2RX
    _U2RXR = 67;            
    _TRISD2 = 0; // RTS
    _RP66R = _RPOUT_U2RTS;
    _TRISD1 = 0; // U2TX
    _RP65R = _RPOUT_U2TX;
    _TRISD4 = 1; // CTS
    _U2CTSR = 68;
    
    // SPI for ADC
    _TRISG6 = 0; // SCK2 is output
    _ANSG6 = 0;
    _TRISG7 = 1; // SDI2 is input
    _ANSG7 = 0;
    _TRISG8 = 0; // SDO2 is output
    _ANSG8 = 0;
    _TRISE5 = 0;     // CS pin
    _ANSE5 = 0;
    _RP85R = _RPOUT_OC4;
    //_RP85R = _RPOUT_SS2;
    _ANSE7 = 0;     // CONV pin
    _TRISE7 = 0;
    _RP87R = _RPOUT_OC15;
    _ANSB4 = 0;     // nEOC
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    // 4V LDO
    _ANSE1 = 0;
    _TRISE1 = 0;
    _RE1 = 1;
    
    // blinky
    _TRISF0 = 0;
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    // 3.3V reference
    _ANSE2 = 0;
    _TRISE2 = 0;
    _RE2 = 1;
    
    // 3.3V ref to PGA
    _ANSE4 = 0;
    _TRISE4 = 0;
    _RE4 = 1;
    
    // address selection
    _ANSB15 = 0;    // A0
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    } else {
        switch(channel_n){
            case 0:
                _RP98R = 0;   // DRV1 signal
                _RF2 = 0;
            case 1:
                _RP99R = 0;   // DRV2 signal
                _RF3 = 0;
            case 2:
                _RP101R = 0;  // DRV3 signal
                _RF4 = 0;
            case 3:
                _RP100R = 0;  // DRV4 signal
                _RF5 = 0;
            default:
                break;
        }
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
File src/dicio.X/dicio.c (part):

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    _LATD8 = 1; 
    
    // UART to PC
    _ANSE5 = 0;            // U2 RTS
    _TRISE5 = 0;
    _RP85R = _RPOUT_U2RTS;
    _ANSE6 = 0;            // U2 CTS
    _U2CTSR = 86;
    _TRISE6 = 1;
    _ANSE7 = 0;            // U2 TX
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    _U2RXR = 119;
    
    // UART to peripheral
    //_TRISF3 = 0;            // U1 RTS
    //_RP99R = _RPOUT_U1RTS;
    _TRISF2 = 0;            // U1 TX
    _RP98R = _RPOUT_U1TX;
    //_TRISD9 = 1;            // U1 CTS
    //_U1CTSR = 73;
    _TRISD10 = 1;           // U1 RX
    _U1RXR = 74;
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    _C1RXR = 83;
    
    // SPI1 configuration   
    _TRISD11 = 1;          // SDI1 
    _SDI1R = 75;
    _TRISF6 = 0;           // SCK1
    _RP102R = _RPOUT_SCK1;
    _TRISD1 = 0;           // SDO1
    _RP65R = _RPOUT_SDO1;
    
    // SPI3 configuration
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
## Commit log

2020-03-23 Footprints.
2020-03-23 PCB boards.
2020-03-23 Code.
2020-03-23 Add ignore file.
2020-03-23 Add README.
2020-03-23 Add licence.
2020-06-10 Add link to published paper.
2020-10-23 Bug fixes and new features.
